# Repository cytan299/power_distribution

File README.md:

# Power Distribution Unit For Astrophotography

by C.Y. Tan 2016

I got really annoyed with the number of power bricks (or wall-warts)
that were required power my astrophotography setup:

* **LX200** 18V power supply. 
* **SBIG ST8300C** 12V power supply.
* **Field DeRotator** 9V power supply.
* **Dew Heater** 5V power supply.
* **Flat field box** 9V power supply.

I decided to consolidate the above into one box but with enough spare
outlets for future expansion.

## Goal

The goal is to build a power distribution unit that replaces all the
wall-warts that are necessary for running my astrophotography
setup. It should have extra outlets so that it can be used to power
other pieces of equipment in the future. All the outlets have to be
fused to protect itself as well as the connected equipment.

## Design

The power distribution unit is powered by a

* [External 240W 19.5V slim PA-9E PC supply](http://www.amazon.com/Original-PA-9E-Replacement-adapter-Notebook/dp/B00AVMYMUG?ie=UTF8&psc=1&redirect=true&ref_=oh_aui_detailpage_o02_s00).

The 19.5V from the above supply is connected to an internal fanless
[HDPLEX 160W ATX DC power supply](http://www.amazon.com/HDPLEX-DC-ATX-Power-Supply-16V-24V/dp/B00KVWHUXW?ie=UTF8&psc=1&redirect=true&ref_=oh_aui_detailpage_o03_s00). The 5V and 12V supplies come directly from
the PLEX. The other 9V is linearly regulated from the 12V and the 15V
is linearly regulated from the 19.5V input voltage. The available voltage
outlets are listed below:

* Three 5V outlets
* Three 12V outlets
* Two 9 V outlets
* One 15 V outlet. I used this to power my LX200 classic. Although the
  front panel says that the voltage should be 18V, sources on the [web](http://www.skymtn.com/mapug-astronomy/MAPUG/Battery1.htm#anchor318436)
  recommend that a lower voltage be used to power it. Therefore I have
  reduced the voltage from 18V to 15V. Note: I was really shocked to
  measure >20V coming out from the Meade power supply for my LX200!

## Support

This is unsupported hardware. Build at your own peril! :)

You can submit questions or bug reports using the
[issues](https://github.com/cytan299/power_distribution/issues) tab on
the right and then click on **NEW**.

Have fun!

## Directory structure

* **case** The case design for the power distribution unit. It
  consists of a 3D STL file for the box and a SVG file for the
  cover. Source code for generating the 3D STL file in [OpenScad](http://www.openscad.org) format
  is included.
* **bom** Bill of materials for 1 power distribution unit.
* **eagle** Eagle schematic and board files.

## Other information

More information can be found in he *README.md* files in each
directory and the [wiki](https://github.com/cytan299/power_distribution/wiki/Power-Distribution-Unit) of this project on github.

## Copyright
All the software, documentation, and hardware that I have written is
copyright 2016 C.Y. Tan.

All software is released under GPLv3

All documentation is released under Creative Commons
Attribution-ShareAlike 3.0 Unported License or GNU Free
Documentation License, Version 1.3

All hardware is released under CERN Hardware Open License v1.2

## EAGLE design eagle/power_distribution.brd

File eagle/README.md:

# Eagle files

These are the eagle files that can be sent to pc board manufacturers to
be made. There is a free version of [eagle](http://cadsoftusa.com)
that can be downloaded to view the designs.

* **power_distribution** This is the schematic and layout of the power
  distribution system.

## Copyright

The schematic and board designs are copyright 2016 C.Y. Tan and
released under the CERN Open Hardware License v1.2

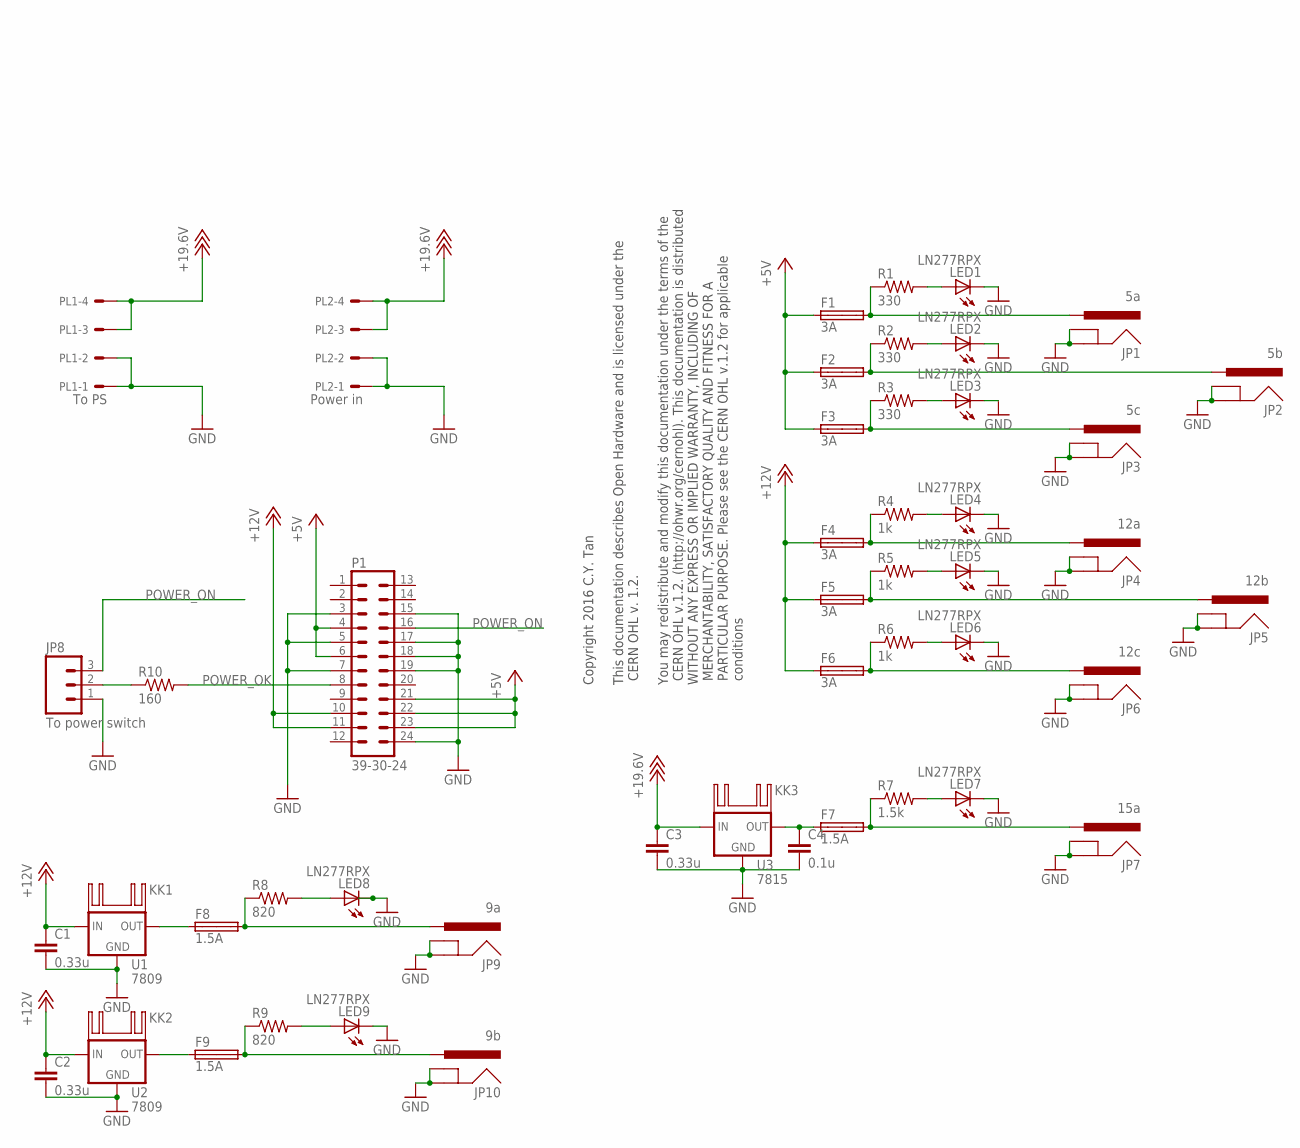
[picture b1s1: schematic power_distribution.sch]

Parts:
C1, C2, C3: 0.33u; CAP-PTH-5MM
C4: 0.1u; CAP-PTH-5MM
F1, F2, F3, F4, F5, F6: 3A; SH32
F7, F8, F9: 1.5A; SH32
JP1: 5a; POWER_JACK_V_PTH
JP2: 5b; POWER_JACK_V_PTH
JP3: 5c; POWER_JACK_V_PTH
JP4: 12a; POWER_JACK_V_PTH
JP5: 12b; POWER_JACK_V_PTH
JP6: 12c; POWER_JACK_V_PTH
JP7: 15a; POWER_JACK_V_PTH
JP8: To power switch; 1X03
JP9: 9a; POWER_JACK_V_PTH
JP10: 9b; POWER_JACK_V_PTH
KK1, KK2, KK3: TO-220_HEATSINK_4W; TO-220-HEATSINK-4W
LED1, LED2, LED3, LED4, LED5, LED6, LED7, LED8, LED9: LN277RPX; LED3MM
P1: 39-30-24; 39-30-?24?
PL1: To PS; 5569-4
PL2: Power in; 5569-4
R1, R2, R3: 330; 0207/10
R4, R5, R6: 1k; 0207/10
R7: 1.5k; 0207/10
R8, R9: 820; 0207/10
R10: 160; 0207/10
U1, U2: 7809; TO-220-ALT
U3: 7815; TO-220-ALT

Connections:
+5V: F1.1A, F2.1A, F3.1A, P1.4, P1.6, P1.21, P1.22, P1.23
+12V: C1.1, C2.1, F4.1A, F5.1A, F6.1A, P1.10, P1.11, U1.IN, U2.IN
+18V: C3.1, PL1.3, PL1.4, PL2.3, PL2.4, U3.IN
GND: C1.2, C2.2, C3.2, C4.2, JP1.GND, JP1.GNDBREAK, JP2.GND, JP2.GNDBREAK, JP3.GND, JP3.GNDBREAK, JP4.GND, JP4.GNDBREAK, JP5.GND, JP5.GNDBREAK, JP6.GND, JP6.GNDBREAK, JP7.GND, JP7.GNDBREAK, JP8.1, JP9.GND, JP9.GNDBREAK, JP10.GND, JP10.GNDBREAK, LED1.K (C), LED2.K (C), LED3.K (C), LED4.K (C), LED5.K (C), LED6.K (C), LED7.K (C), LED8.K (C), LED9.K (C), P1.3, P1.5, P1.7, P1.15, P1.17, P1.18, P1.19, P1.24, PL1.1, PL1.2, PL2.1, PL2.2, U1.GND, U2.GND, U3.GND
unnamed: F1.2A, JP1.PWR, R1.1
unnamed: F2.2A, JP2.PWR, R2.1
unnamed: F3.2A, JP3.PWR, R3.1
unnamed: LED1.A, R1.2
unnamed: LED2.A, R2.2
unnamed: LED3.A, R3.2
unnamed: F4.2A, JP4.PWR, R4.1
unnamed: F5.2A, JP5.PWR, R5.1
unnamed: F6.2A, JP6.PWR, R6.1
unnamed: LED4.A, R4.2
unnamed: LED5.A, R5.2
unnamed: LED6.A, R6.2
unnamed: F8.1A, U1.OUT
unnamed: F7.2A, JP7.PWR, R7.1
unnamed: LED7.A, R7.2
unnamed: F8.2A, JP9.PWR, R8.1
unnamed: LED8.A, R8.2
unnamed: JP8.2, R10.1
unnamed: F9.1A, U2.OUT
unnamed: F9.2A, JP10.PWR, R9.1
unnamed: LED9.A, R9.2
unnamed: C4.1, F7.1A, U3.OUT
POWER_OK: P1.8, R10.2
POWER_ON: JP8.3, P1.16

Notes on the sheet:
Copyright 2016 C.Y. Tan This documentation describes Open Hardware and is licensed under the CERN OHL v. 1.2. You may redistribute and modify this documentation under the terms of the CERN OHL v.1.2. (http://ohwr.org/cernohl). This documentation is distributed WITHOUT ANY EXPRESS OR IMPLIED WARRANT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

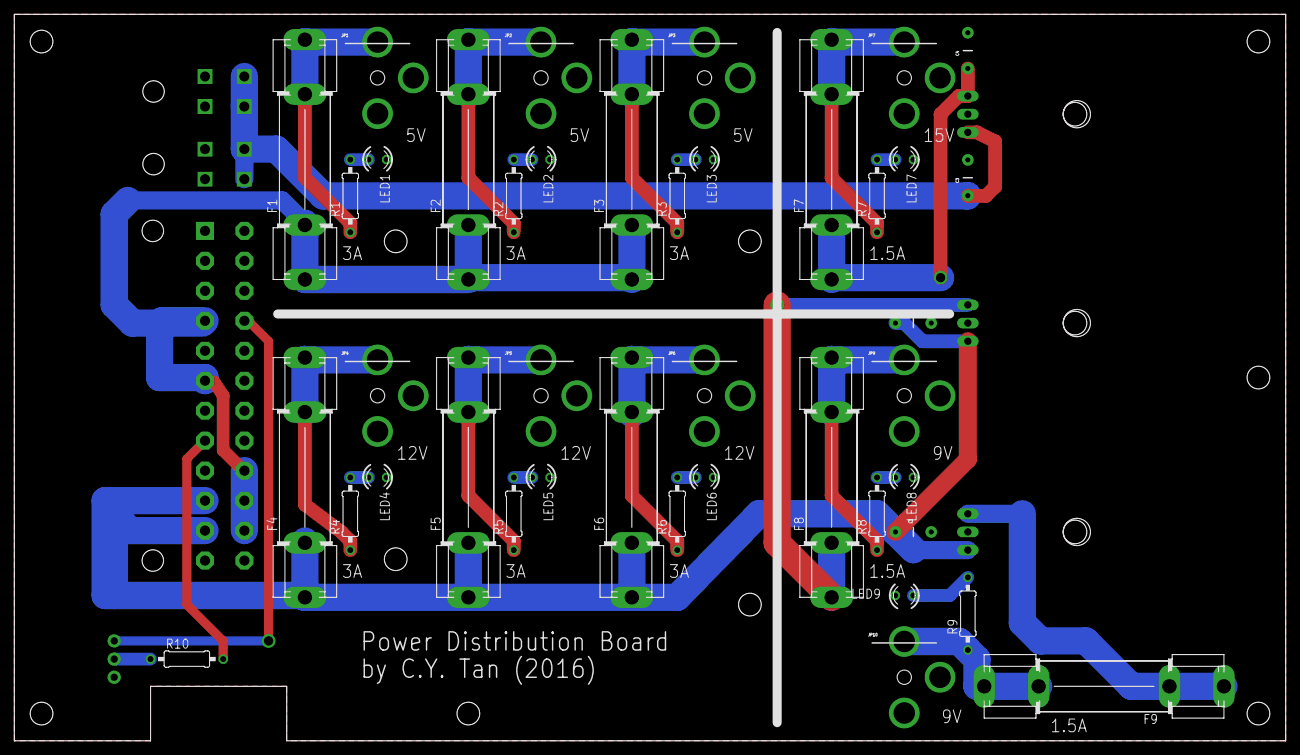
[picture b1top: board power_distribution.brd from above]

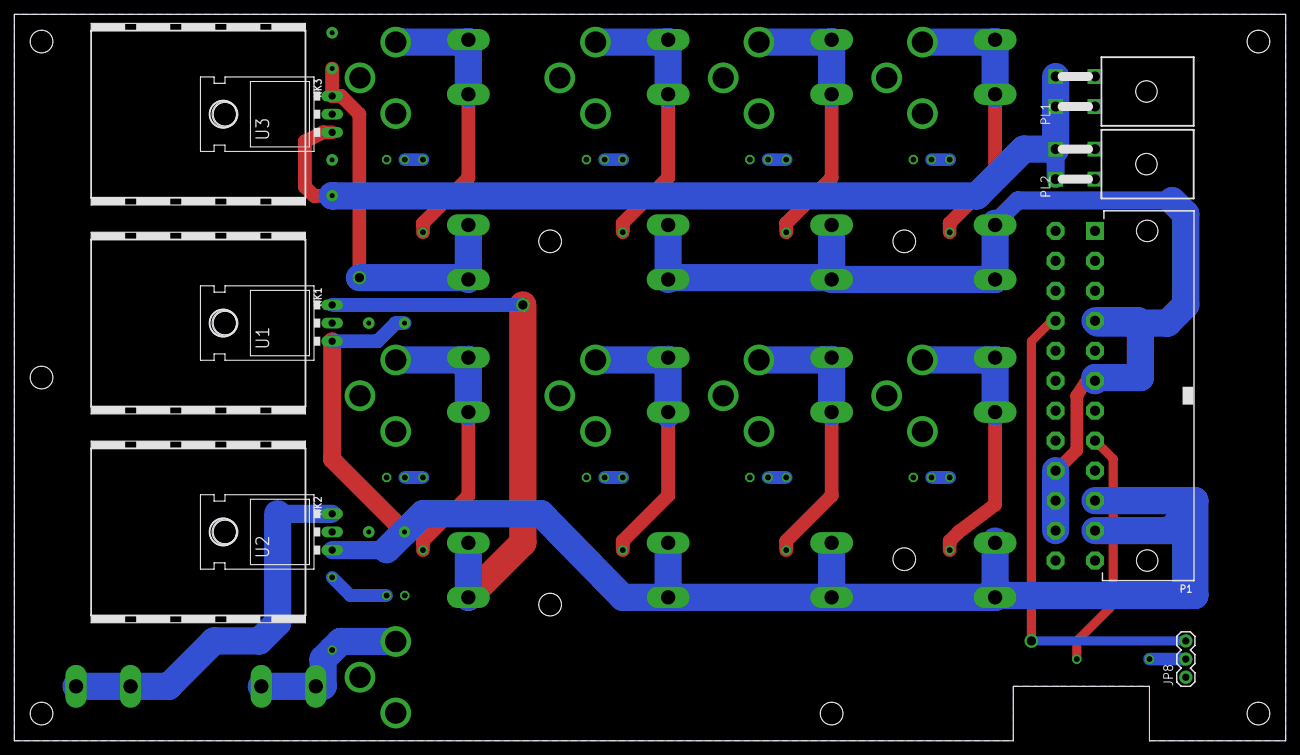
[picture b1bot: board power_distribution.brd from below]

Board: 2 copper layers, 177.8 x 101.6 mm, 51 parts (10 on the bottom side), 28 nets.

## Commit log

2016-04-03 Power Distribution Unit for Astrophotography
2016-04-03 README.md: Updated link to photograph of power distribution unit. Plus small edits
2016-04-03 README.md: Fixed typos
2016-04-03 Updated README.md and case/README.md
2016-04-03 Updated README.md to point to power supply specs
2016-04-03 Fixed README.md typo
2016-04-03 eagle: Added CERN open hardware license
2016-04-14 case: Updated GNU license in 3D_case.scad

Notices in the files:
parts and their libraries:
SparkFun-Connectors: Licensing: Creative Commons ShareAlike 4.0 International - https://creativecommons.org/licenses/by-sa/4.0
